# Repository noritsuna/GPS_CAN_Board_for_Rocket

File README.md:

# GPS_CAN_Board_for_Rocket
GPS & CAN Board for Rocket.

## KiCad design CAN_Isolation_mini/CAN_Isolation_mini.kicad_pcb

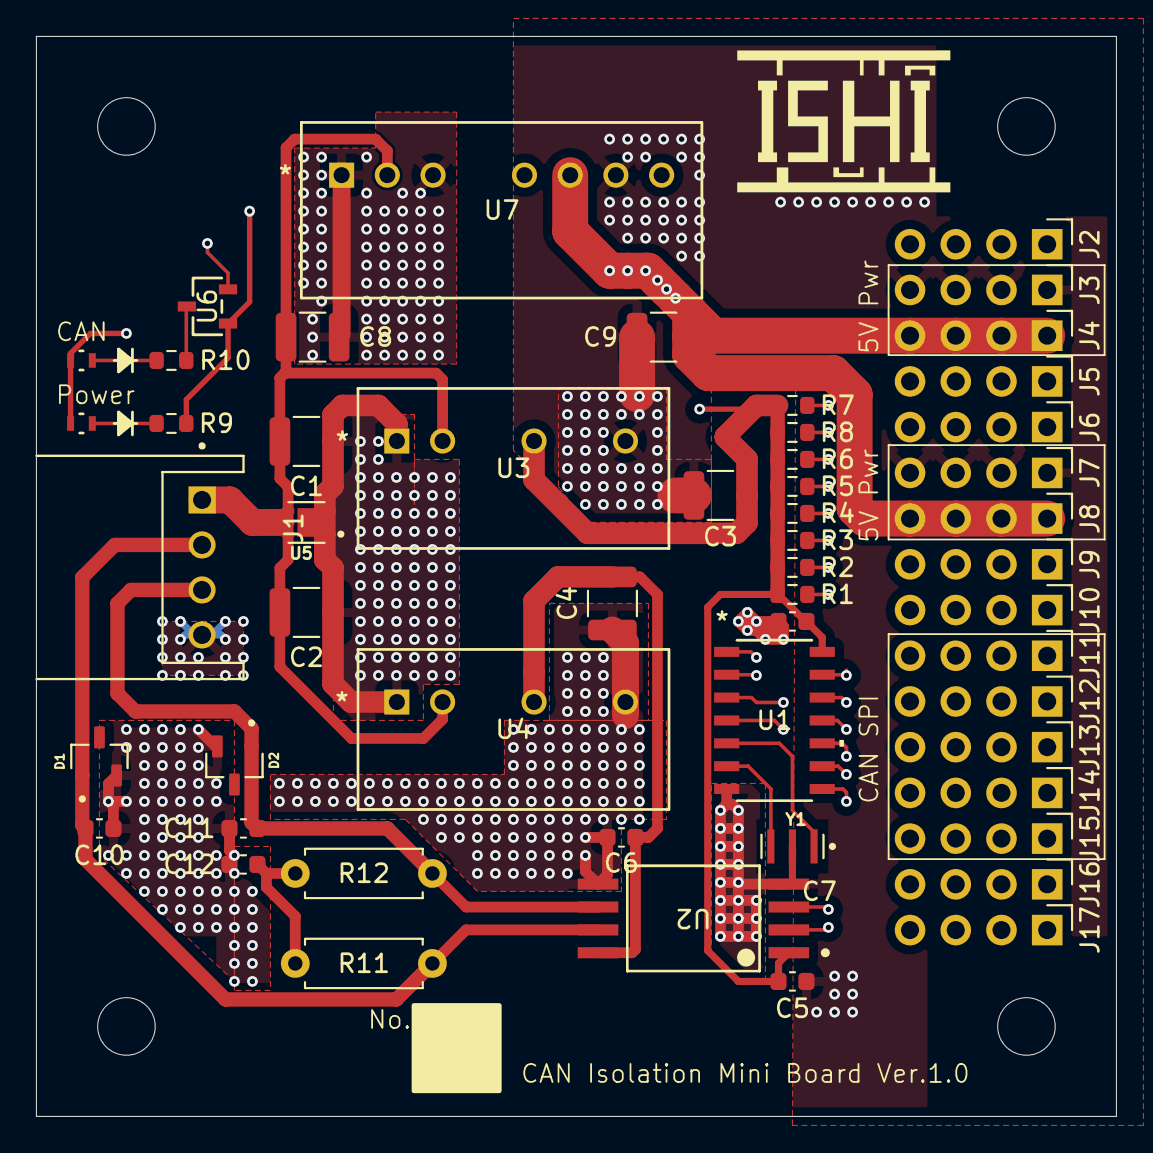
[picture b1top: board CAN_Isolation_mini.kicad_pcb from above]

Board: 4 copper layers, 60.0 x 60.0 mm, 53 parts (0 on the bottom side), 26 nets.

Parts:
C1, C2, C3, C4, C8, C9: 22u; C_1210_3225Metric
C5, C6, C7: 100n; C_0603_1608Metric
C10, C11: 47p; C_0603_1608Metric
C12: 4700p; C_0603_1608Metric
D1, D2: MMBZ27VCLT1G; SOT95P237X111-3N
J1: S4B-XH-A; JST_S4B-XH-A
J2, J3, J4, J5, J6, J7, J8, J9, J10, J11, J12, J13, J14, J15, J16, J17: Conn_01x04_Pin; PinHeader_1x04_P2.54mm_Vertical_noSilk
LED1, LED2: SMLD12EN1WT86
R1, R2, R3, R4, R5, R6, R7, R8: 10k; R_0603_1608Metric
R9, R10: 200; R_0603_1608Metric
R11, R12: 60.4; R_Axial_DIN0207_L6.3mm_D2.5mm_P7.62mm_Horizontal
U1: MCP2518FDT-H/SL; SOIC14_150MIL_SL_MCH
U2: ISO1042QDWVRQ1; DWV0008A-IPC_A
U3: MGS3123R3; MGS3_COS
U4: MGS1R51205; MGS3_COS
U5: TVS1800DRVR; SON65P200X200X80-7N
U6: DTC114ECAHZGT116; TRANS_DTCZCAHZGT_ROM
U7: MGS102405; SIP7_MGS10_COS
Y1: CSTNE20M0V530000R0; OSC_CSTNE20M0V530000R0

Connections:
+3.3VP: C3.1, C5.1, C7.2, LED1.2, LED2.2, R1.1, R2.1, R3.1, R4.1, R5.1, R6.1, R7.1, R8.1, U1.14 (VDD), U2.1 (VCC1), U3.3 (+VOUT)
+5VCAN: C4.1, C6.1, U2.8 (VCC2), U4.3 (+VOUT)
+5VP: C9.1, J4.1, J4.2, J4.3, J4.4, J8.1, J8.2, J8.3, J8.4, U7.6 (+VOUT)
BAT_12V: C1.1, C2.1, C8.1, J1.1, U3.2 (+VIN), U4.2 (+VIN), U5.4 (IN), U5.5 (IN), U5.6 (IN), U7.2 (+VIN)
BAT_GND: C1.2, C2.2, C8.2, J1.4, U3.1 (-VIN), U4.1 (-VIN), U5.1 (GND), U5.2 (GND), U5.3 (GND), U5.7 (GND), U7.1 (-VIN), U7.3 (RC)
CAN_CLK: R7.2, U1.3 (CLKO/SOF)
CAN_CS: J12.1, J12.2, J12.3, J12.4, R1.2, U1.13 (NCS)
CAN_GPIO0: R5.2, U1.9 (*INT0/GPIO0/XSTBY)
CAN_GPIO1: R6.2, U1.8 (*INT1/GPIO1)
CAN_H: C10.1, D1.1, J1.2, R11.1, U2.7 (CANH)
CAN_INT: R8.2, U1.4 (*INT)
CAN_L: C11.2, D2.1, J1.3, R12.2, U2.6 (CANL)
CAN_LED: J11.1, J11.2, J11.3, J11.4, U6.2
CAN_SCK: J15.1, J15.2, J15.3, J15.4, R4.2, U1.10 (SCK)
CAN_SDI: J14.1, J14.2, J14.3, J14.4, R3.2, U1.11 (SDI)
CAN_SDO: J13.1, J13.2, J13.3, J13.4, R2.2, U1.12 (SDO)
GND_5VCAN: C4.2, C6.2, C10.2, C11.1, C12.2, D1.2, D2.2, U2.5 (GND2), U4.4 (-VOUT)
GND_VP: C3.2, C5.2, C7.1, C9.2, J3.1, J3.2, J3.3, J3.4, J7.1, J7.2, J7.3, J7.4, R9.2, U1.7 (VSS), U2.4 (GND1), U3.4 (-VOUT), U6.1, U7.7 (-VOUT), Y1.2
unnamed: C12.1, R11.2, R12.1
unnamed: LED1.1, R9.1
unnamed: LED2.1, R10.1
unnamed: R10.2, U6.3
unnamed: U1.6 (OSC1), Y1.3
unnamed: U1.5 (OSC2), Y1.1
unnamed: U1.2 (RXCAN), U2.3 (RXD)
unnamed: U1.1 (TXCAN), U2.2 (TXD)

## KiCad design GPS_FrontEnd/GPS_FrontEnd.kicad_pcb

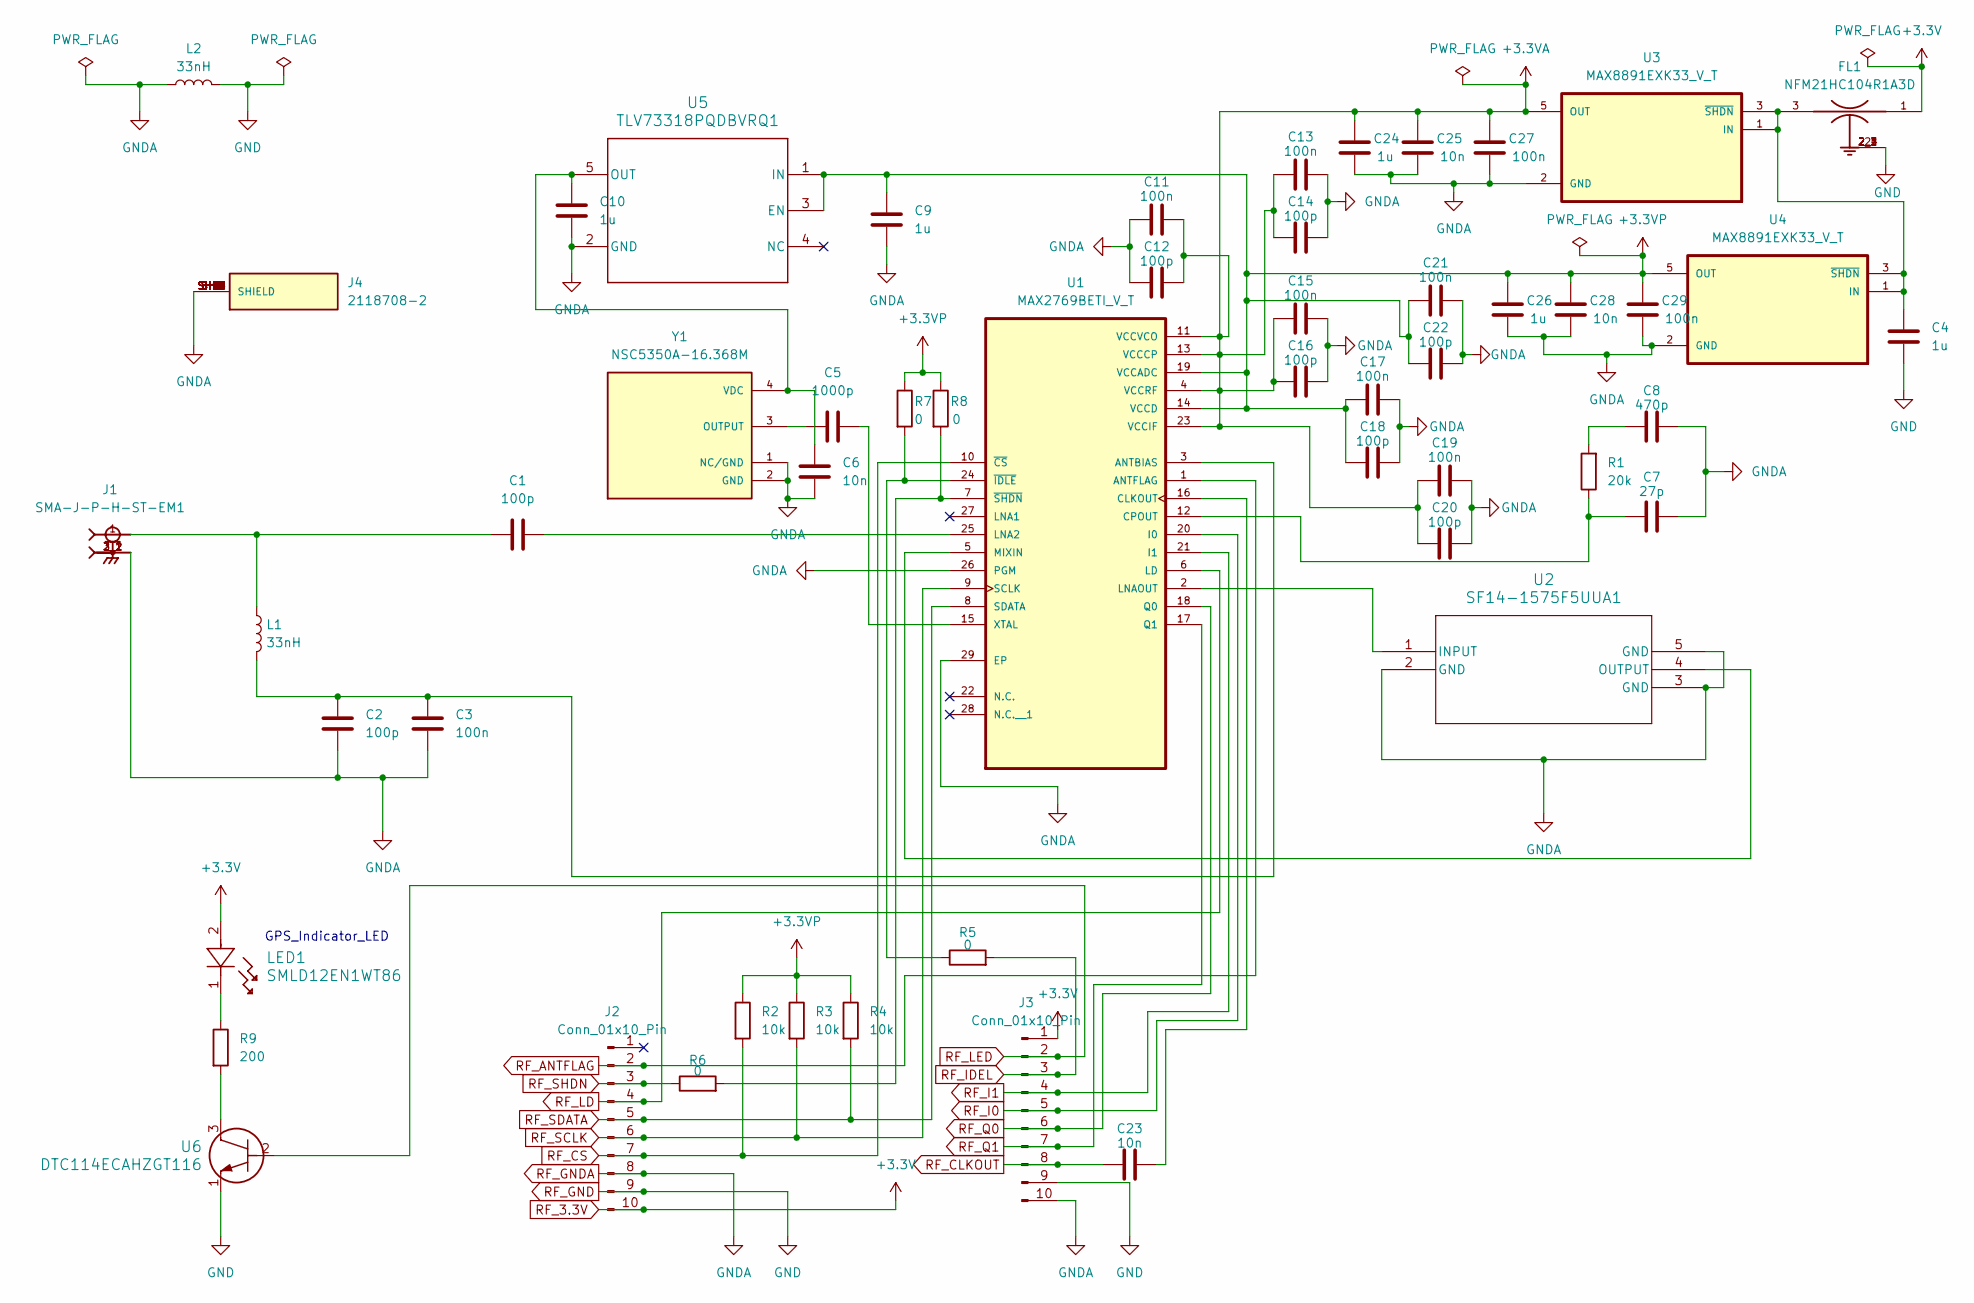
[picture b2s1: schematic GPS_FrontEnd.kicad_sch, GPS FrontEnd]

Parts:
C1, C2, C12, C14, C16, C18, C20, C22: 100p; C_0603_1608Metric
C3: 100n; C_1111_2828Metric
C4, C9, C10, C24, C26: 1u; C_0603_1608Metric
C5: 1000p; C_1210_3225Metric
C6: 10n; C_0505_1313Metric
C7: 27p; C_0603_1608Metric
C8: 470p; C_0505_1313Metric
C11, C13, C15, C17, C19, C21, C27, C29: 100n; C_0603_1608Metric
C23, C25, C28: 10n; C_0603_1608Metric
FL1: NFM21HC104R1A3D; FIL_NFM21HC104R1A3D
J1: SMA-J-P-H-ST-EM1; SAMTEC_SMA-J-P-H-ST-EM1; PARTREV G
J2, J3: Conn_01x10_Pin; PinHeader_1x10_P2.54mm_Vertical
J4: 2118708-2; TE_2118708-2; PARTREV A2
L1, L2: 33nH; L_0603_1608Metric
LED1: SMLD12EN1WT86
R1: 20k; R_0603_1608Metric
R2, R3, R4: 10k; R_0603_1608Metric
R5, R6, R7, R8: 0; R_0603_1608Metric
R9: 200; R_0603_1608Metric
U1: MAX2769BETI_V_T; QFN50P500X500X80-29N
U2: SF14-1575F5UUA1; SO4_1411-SAW_1p1x1p4_KAV
U3, U4: MAX8891EXK33_V_T; SOT65P210X110-5N
U5: TLV73318PQDBVRQ1; DBV0005A_N
U6: DTC114ECAHZGT116; TRANS_DTCZCAHZGT_ROM
Y1: NSC5350A-16.368M; OSC_TX22-18025S-19.200-R; PARTREV Nov 07, 2023

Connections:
+3.3VA: C11.2, C12.2, C13.2, C14.2, C15.1, C16.1, C19.1, C20.1, C24.1, C25.1, C27.1, U1.4 (VCCRF), U1.11 (VCCVCO), U1.13 (VCCCP), U1.23 (VCCIF), U3.5 (OUT)
+3.3VP: C9.1, C17.2, C18.2, C21.1, C22.1, C26.1, C28.1, C29.1, R2.1, R3.1, R4.1, R7.1, R8.1, U1.14 (VCCD), U1.19 (VCCADC), U4.5 (OUT), U5.1 (IN), U5.3 (EN)
unnamed: C1.1, J1.1, L1.1
unnamed: C8.1, R1.2
unnamed: LED1.1, R9.1
unnamed: R9.2, U6.3
unnamed: C2.1, C3.1, L1.2, U1.3 (ANTBIAS)
unnamed: C23.2, U1.16 (CLKOUT)
unnamed: C7.1, R1.1, U1.12 (CPOUT)
unnamed: C1.2, U1.25 (LNA2)
unnamed: U1.2 (LNAOUT), U2.1 (INPUT)
unnamed: U1.5 (MIXIN), U2.4 (OUTPUT)
unnamed: C5.2, U1.15 (XTAL)
unnamed: R5.1, R7.2, U1.24 (~IDLE)
unnamed: R6.2, R8.2, U1.7 (~SHDN)
unnamed: C4.1, FL1.3, U3.1 (IN), U3.3 (~SHDN), U4.1 (IN), U4.3 (~SHDN)
unnamed: C6.1, C10.1, U5.5 (OUT), Y1.4 (VDC)
unnamed: C5.1, Y1.3 (OUTPUT)
RF_3.3V: FL1.1, J2.10, J3.1, LED1.2
RF_ANTFLAG: J2.2, U1.1 (ANTFLAG)
RF_CLKOUT: C23.1, J3.8
RF_CS: J2.7, R2.2, U1.10 (~CS)
RF_GND: C4.2, FL1.2, FL1.2_1, FL1.2_2, FL1.2_3, FL1.2_4, J2.9, J3.9, L2.2, U6.1
RF_GNDA: C2.2, C3.2, C6.2, C7.2, C8.2, C9.2, C10.2, C11.1, C12.1, C13.1, C14.1, C15.2, C16.2, C17.1, C18.1, C19.2, C20.2, C21.2, C22.2, C24.2, C25.2, C26.2, C27.2, C28.2, C29.2, J1.2_1, J1.2_2, J1.3_1, J1.3_2, J2.8, J3.10, J4.SH1 (SHIELD), J4.SH2 (SHIELD), J4.SH3 (SHIELD), J4.SH4 (SHIELD), J4.SH5 (SHIELD), J4.SH6 (SHIELD), J4.SH7 (SHIELD), J4.SH8 (SHIELD), J4.SH9 (SHIELD), J4.SH10 (SHIELD), J4.SH11 (SHIELD), J4.SH12 (SHIELD), J4.SH13 (SHIELD), J4.SH14 (SHIELD), J4.SH15 (SHIELD), J4.SH16 (SHIELD), L2.1, U1.26 (PGM), U1.29 (EP), U2.2 (GND), U2.3 (GND), U2.5 (GND), U3.2 (GND), U4.2 (GND), U5.2 (GND), Y1.1 (NC/GND), Y1.2 (GND)
RF_I0: J3.5, U1.20 (I0)
RF_I1: J3.4, U1.21 (I1)
RF_IDEL: J3.3, R5.2
RF_LD: J2.4, U1.6 (LD)
RF_LED: J3.2, U6.2
RF_Q0: J3.6, U1.18 (Q0)
RF_Q1: J3.7, U1.17 (Q1)
RF_SCLK: J2.6, R3.2, U1.9 (SCLK)
RF_SDATA: J2.5, R4.2, U1.8 (SDATA)
RF_SHDN: J2.3, R6.1

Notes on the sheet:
GPS_Indicator_LED

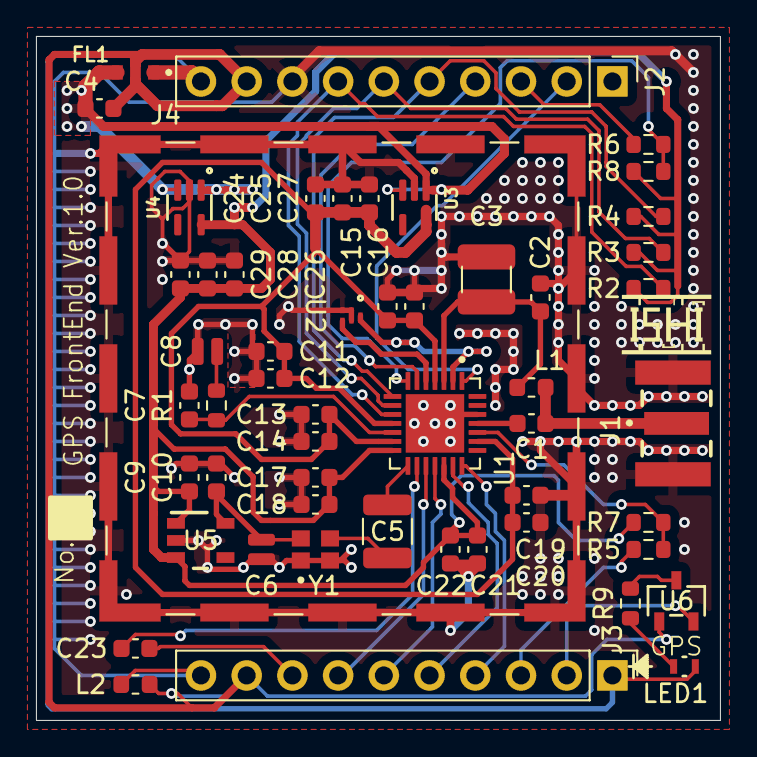
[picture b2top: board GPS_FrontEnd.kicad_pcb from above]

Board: 2 copper layers, 38.0 x 38.0 mm, 53 parts (0 on the bottom side), 34 nets.

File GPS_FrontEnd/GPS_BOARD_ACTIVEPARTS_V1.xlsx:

出荷時に原産国が変わる場合があります。
表示されているHTSUSおよびECCN情報は情報提供のみを目的としたもので、分類の正確性や信頼性を表明または保証するものではありません。すべての情報は「現状の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
インデックス | メーカー品番 | メーカー名 | 商品概要 | リードタイム | 入手性 | 在庫状況 | 仕損率 | リクエスト数量1 | パック数量1 | パックタイプ1 | Digi-Key品番1 | 単価1 | 金額1 | 最小発注数量1 | 客先参照品番 | リクエスト品番 | リードタイム（週） | データシート | 参照名 | 米国輸入関税 | メモ | 部品状況 | RoHSステータス | 湿度感度レベル（MSL） | ECCN | HTSUS | 原産国 | 環境規制対応 | オリジナル品番 | 画像 | 製品に関する注意事項
1 | MAX2769BETI/V+T | Analog Devices Inc./Maxim Integrated | RF RCVR GPS 1575.42MHZ 28TQFN |  | 1,961 | 在庫品目 |  | 1 | 1 | Cut Tape (CT) | 175-MAX2769BETI/V+TCT-ND | 11.32000 | $11.32 | 1 |  | 175-MAX2769BETI/V+TCT-ND | 10 | https://mm.digikey.com/Volume0/opasdata/d220001/medias/docus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 |  | N/A |  | アクティブ | ROHS3対応 | 1（無制限） | 7A994 | 8542.39.0060 | Taiwan | https://www.maximintegrated.com/content/dam/files/design/emm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 | 175-MAX2769BETI/V+TCT-ND | https://mm.digikey.com/Volume0/opasdata/d220001/medias/image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 | キャンセルや返品はできません.
2 | MAX8891EXK33/V+T | Analog Devices Inc./Maxim Integrated | IC REG LINEAR 3.3V 150MA SC-70-6 |  | 3,895 | 在庫品目 |  | 2 | 2 | Cut Tape (CT) | 175-MAX8891EXK33/V+TCT-ND | 2.11000 | $4.22 | 1 |  | 175-MAX8891EXK33/V+TCT-ND | 10 | https://www.analog.com/media/en/technical-documentation/data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 |  | N/A |  | アクティブ | ROHS3対応 | 1（無制限） | EAR99 | 8542.39.0090 | Malaysia | https://www.maximintegrated.com/content/dam/files/design/emm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 | 175-MAX8891EXK33/V+TCT-ND | https://mm.digikey.com/Volume0/opasdata/d220001/medias/image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
3 | B39162B4348P810 | Qualcomm (RF front-end (RFFE) filters) | FILTER SAW 1.582GHZ 5-SMD |  | 778 | 在庫品目 |  | 1 | 1 | Cut Tape (CT) | B39162B4348P810CT-ND | 1.49000 | $1.49 | 1 |  | B39162B4348P810CT-ND | 8 | https://mm.digikey.com/Volume0/opasdata/d220001/medias/docus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 |  | N/A |  | アクティブ | ROHS3対応 | 2A（4週間） | EAR99 | 8541.60.0080 | Singapore |  | B39162B4348P810CT-ND | https://mm.digikey.com/Volume0/opasdata/d220001/medias/image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
4 | SMA-J-P-H-ST-EM1 | Samtec Inc. | CONN SMA JACK STR 50OHM EDGE MNT | 2025年10月16日に入荷予定：1個 | 0 | 通常在庫 |  | 1 | 1 | Tray | SAM8857-ND | 2.43000 | $2.43 | 1 |  | SAM8857-ND | 6 | https://mm.digikey.com/Volume0/opasdata/d220001/medias/docus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 |  | N/A |  | アクティブ | ROHS3対応 | 1（無制限） | EAR99 | 8536.69.4010 | Taiwan |  | SAM8857-ND | https://mm.digikey.com/Volume0/opasdata/d220001/medias/image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
5 | NSC5350A-16.368M | NDK (NIHON DEMPA KOGYO CO., LTD) | XTAL OSC TCXO 16.3680MHZ SMD |  | 867 | 在庫品目 |  | 1 | 1 | Cut Tape (CT) | 644-NSC5350A-16.368MCT-ND | 1.85000 | $1.85 | 1 |  | 644-NSC5350A-16.368MCT-ND | 24 | https://www.ndk.com/en/products/upload/lineup/pdf/NDKT03-000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 |  | N/A |  | アクティブ | ROHS3対応 | 2（1年間） | EAR99 | 8542.39.0090 | Japan |  | 644-NSC5350A-16.368MCT-ND | https://mm.digikey.com/Volume0/opasdata/d220001/medias/image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
6 | TLV73318PQDBVRQ1 | Texas Instruments | IC REG LINEAR 1.8V 300MA SOT23-5 |  | 16,868 | 在庫品目 |  | 1 | 1 | Cut Tape (CT) | 296-TLV73318PQDBVRQ1CT-ND | 0.45000 | $0.45 | 1 |  | 296-TLV73318PQDBVRQ1CT-ND | 12 | https://www.ti.com/general/docs/suppproductinfo.tsp?distId=1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 |  | N/A |  | アクティブ | ROHS3対応 | 1（無制限） | EAR99 | 8542.39.0090 | Philippines |  | 296-TLV73318PQDBVRQ1CT-ND | https://mm.digikey.com/Volume0/opasdata/d220001/medias/image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
7 | SF14-1575F5UUA1 | KYOCERA AVX | FILTER SAW 1.575GHZ 5-SMD |  | 8,991 | 個在庫あり - 非在庫保有商品 |  | 1 | 1 | Cut Tape (CT) | 478-SF14-1575F5UUA1CT-ND | 0.61000 | $0.61 | 1 |  | 478-SF14-1575F5UUA1CT-ND | 16 | https://mm.digikey.com/Volume0/opasdata/d220001/medias/docus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 |  | N/A |  | 生産中止品 | ROHS3対応 | 3（168時間） | 7A994 | 8541.60.0080 | Japan | https://ele.kyocera.com/assets/products/saw-device/environme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|ht… | 478-SF14-1575F5UUA1CT-ND | https://mm.digikey.com/Volume0/opasdata/d220001/medias/image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
8 | DTC114ECAHZGT116 | Rohm Semiconductor | TRANS PREBIAS NPN 0.1A SST3 |  | 2,933 | 在庫品目 |  | 1 | 1 | Cut Tape (CT) | DTC114ECAHZGT116CT-ND | 0.17000 | $0.17 | 1 |  | DTC114ECAHZGT116CT-ND | 18 | https://www.rohm.co.jp/datasheet?p=DTC114ECAHZG&dist=Digi-ke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 |  | N/A |  | アクティブ | ROHS3対応 | 1（無制限） | EAR99 | 8541.21.0075 | South Korea | https://fscdn.rohm.com/en/techdata_basic/transistor/anti_whi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 | DTC114ECAHZGT116CT-ND | https://mm.digikey.com/Volume0/opasdata/d220001/medias/image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
9 | 2118708-2 | TE Connectivity AMP Connectors | RF SHIELD 1.032"X1.032" SMD 1PC |  | 9,237 | 在庫品目 |  | 1 | 1 | Cut Tape (CT) | A126142CT-ND | 1.05000 | $1.05 | 1 |  | A126142CT-ND | 5 | https://www.te.com/commerce/DocumentDelivery/DDEController?A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 |  | N/A |  | アクティブ | RoHS対応 | 適用外 | EAR99 | 8529.90.9800 | China |  | A126142CT-ND | https://mm.digikey.com/Volume0/opasdata/d220001/medias/image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

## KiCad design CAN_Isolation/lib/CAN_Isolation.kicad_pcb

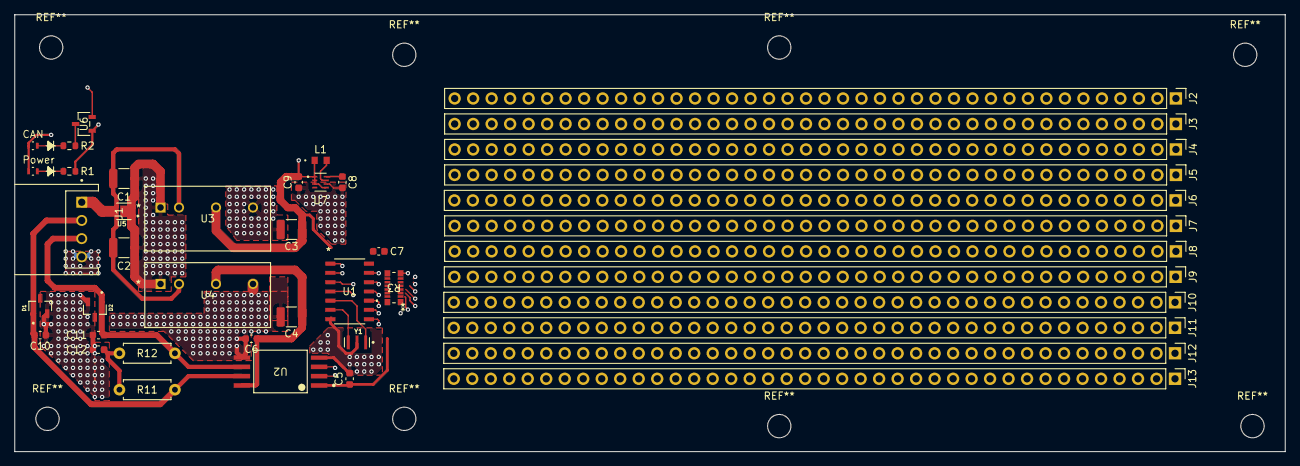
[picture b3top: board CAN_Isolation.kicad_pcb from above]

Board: 4 copper layers, 174.5 x 60.0 mm, 43 parts (0 on the bottom side), 26 nets.

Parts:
C1, C2, C3, C4: 22u; C_1210_3225Metric
C5, C6, C7, C8, C9: 100n; C_0603_1608Metric
C10, C11: 47p; C_0603_1608Metric
C12: 4700p; C_0603_1608Metric
D1, D2: MMBZ27VCLT1G; SOT95P237X111-3N
J1: S4B-XH-A; JST_S4B-XH-A
J2, J3, J4, J5, J6, J7, J8, J9, J10, J11, J12, J13: Conn_01x40_Pin; PinHeader_1x40_P2.54mm_Vertical
L1: 0.47uH; IND_LCCN_1608KK_TAY
LED1, LED2: SMLD12EN1WT86
R1, R2: 200; R_0603_1608Metric
R3: EXB-2HV103JV; RES_EXB2HV
R11, R12: 60.4; R_Axial_DIN0207_L6.3mm_D2.5mm_P7.62mm_Horizontal
U1: MCP2518FDT-H/SL; SOIC14_150MIL_SL_MCH
U2: ISO1042QDWVRQ1; DWV0008A-IPC_A
U3: MGS3123R3; MGS3_COS
U4: MGS1R51205; MGS3_COS
U5: TVS1800DRVR; SON65P200X200X80-7N
U6: DTC114ECAHZGT116; TRANS_DTCZCAHZGT_ROM
U7: TPS610333QDRLRQ1; SOT-5X3-8_DRL_TEX
Y1: CSTNE20M0V530000R0; OSC_CSTNE20M0V530000R0

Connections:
+3.3VP: C3.1, C5.1, C7.2, C9.1, L1.1, LED1.2, LED2.2, R3.9, R3.10, R3.11, R3.12, R3.13, R3.14, R3.15, R3.16, U1.14 (VDD), U2.1 (VCC1), U3.3 (+VOUT), U7.1 (VIN), U7.2 (EN), U7.3 (MODE), U7.5 (FB)
+5VCAN: C4.1, C6.1, U2.8 (VCC2), U4.3 (+VOUT)
+5VD: C8.1, U7.8 (VOUT)
BAT_12V: C1.1, C2.1, J1.1, U3.2 (+VIN), U4.2 (+VIN), U5.4 (IN), U5.5 (IN), U5.6 (IN)
BAT_GND: C1.2, C2.2, J1.4, U3.1 (-VIN), U4.1 (-VIN), U5.1 (GND), U5.2 (GND), U5.3 (GND), U5.7 (GND)
CAN_CLK: R3.7, U1.3 (CLKO/SOF)
CAN_CS: R3.8, U1.13 (NCS)
CAN_GPIO0: R3.2, U1.9 (*INT0/GPIO0/XSTBY)
CAN_GPIO1: R3.1, U1.8 (*INT1/GPIO1)
CAN_H: C10.1, D1.1, J1.2, R11.1, U2.7 (CANH)
CAN_INT: R3.5, U1.4 (*INT)
CAN_L: C11.2, D2.1, J1.3, R12.2, U2.6 (CANL)
CAN_SCK: R3.3, U1.10 (SCK)
CAN_SDI: R3.4, U1.11 (SDI)
CAN_SDO: R3.6, U1.12 (SDO)
GND_3P3: C3.2, C5.2, C7.1, C8.2, C9.2, R1.2, U1.7 (VSS), U2.4 (GND1), U3.4 (-VOUT), U6.1, U7.6 (GND), Y1.2
GND_5VCAN: C4.2, C6.2, C10.2, C11.1, C12.2, D1.2, D2.2, U2.5 (GND2), U4.4 (-VOUT)
unnamed: C12.1, R11.2, R12.1
unnamed: LED1.1, R1.1
unnamed: LED2.1, R2.1
unnamed: R2.2, U6.3
unnamed: U1.6 (OSC1), Y1.3
unnamed: U1.5 (OSC2), Y1.1
unnamed: U1.2 (RXCAN), U2.3 (RXD)
unnamed: U1.1 (TXCAN), U2.2 (TXD)
unnamed: L1.2, U7.7 (SW)

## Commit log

2025-09-09 1st Commit.
    1st Commit.
2025-09-15 Add CAN mini board.
    Add CAN mini board.
2025-09-15 Add 3.3V version.
    Add 3.3V version.
2025-09-15 Fix VIA for 5&3.3V line.
    Fix VIA for 5&3.3V line.
2025-09-17 Add XT60 version.
    Add XT60 version.
2025-09-17 Add diode for servo line.
    Add diode for servo line.
2025-09-17 Change board size.
    Change board size.
2025-09-17 Fix file name.
    Fix file name.
2025-09-17 Fix XT60 line.
    Fix XT60 line.
2025-09-18 Change connector.
    Change connector.
